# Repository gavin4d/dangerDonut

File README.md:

# Danger Donut

Danger Donut is a work-in-progress 150 gram melty brain combat robot.

This repository contains:
* Code for the operations of the bot
* Code for the IR beacon modulation
* ESC configs
* Main board PCB design
* IR beacon PCB design
* POV display artwork

Links:
* [Bill of Materials](https://docs.google.com/spreadsheets/d/1dkWNEsBBoqDzMkqIhuPgsKdvJ411szMJZwjo1TRifCI/edit?usp=sharing)
* [Full Robot CAD](https://cad.onshape.com/documents/b2161876893824b000416544/w/ad922c252fa114c5bccae0f6/e/2d73a76351a9b656583123fa?renderMode=0&uiState=650de28cdfa14238780e15cb)
* [IR Beacon CAD for Xbox controller](https://cad.onshape.com/documents/fe686b6ebfe56c60cbf11a52/w/a5235571450e0940f943c7f9/e/e1fc86eb24f972fd453b77be?renderMode=0&uiState=650de2660cc6cc1104d13ac3)
* [Transport Box CAD](https://cad.onshape.com/documents/9698310442d8aade0d12c8ac/w/1dfdf825a6ce81e21ee8f0cf/e/f9df83b772e96680fdb5acf9?renderMode=0&uiState=65457ec2115608246b0ef2cf)

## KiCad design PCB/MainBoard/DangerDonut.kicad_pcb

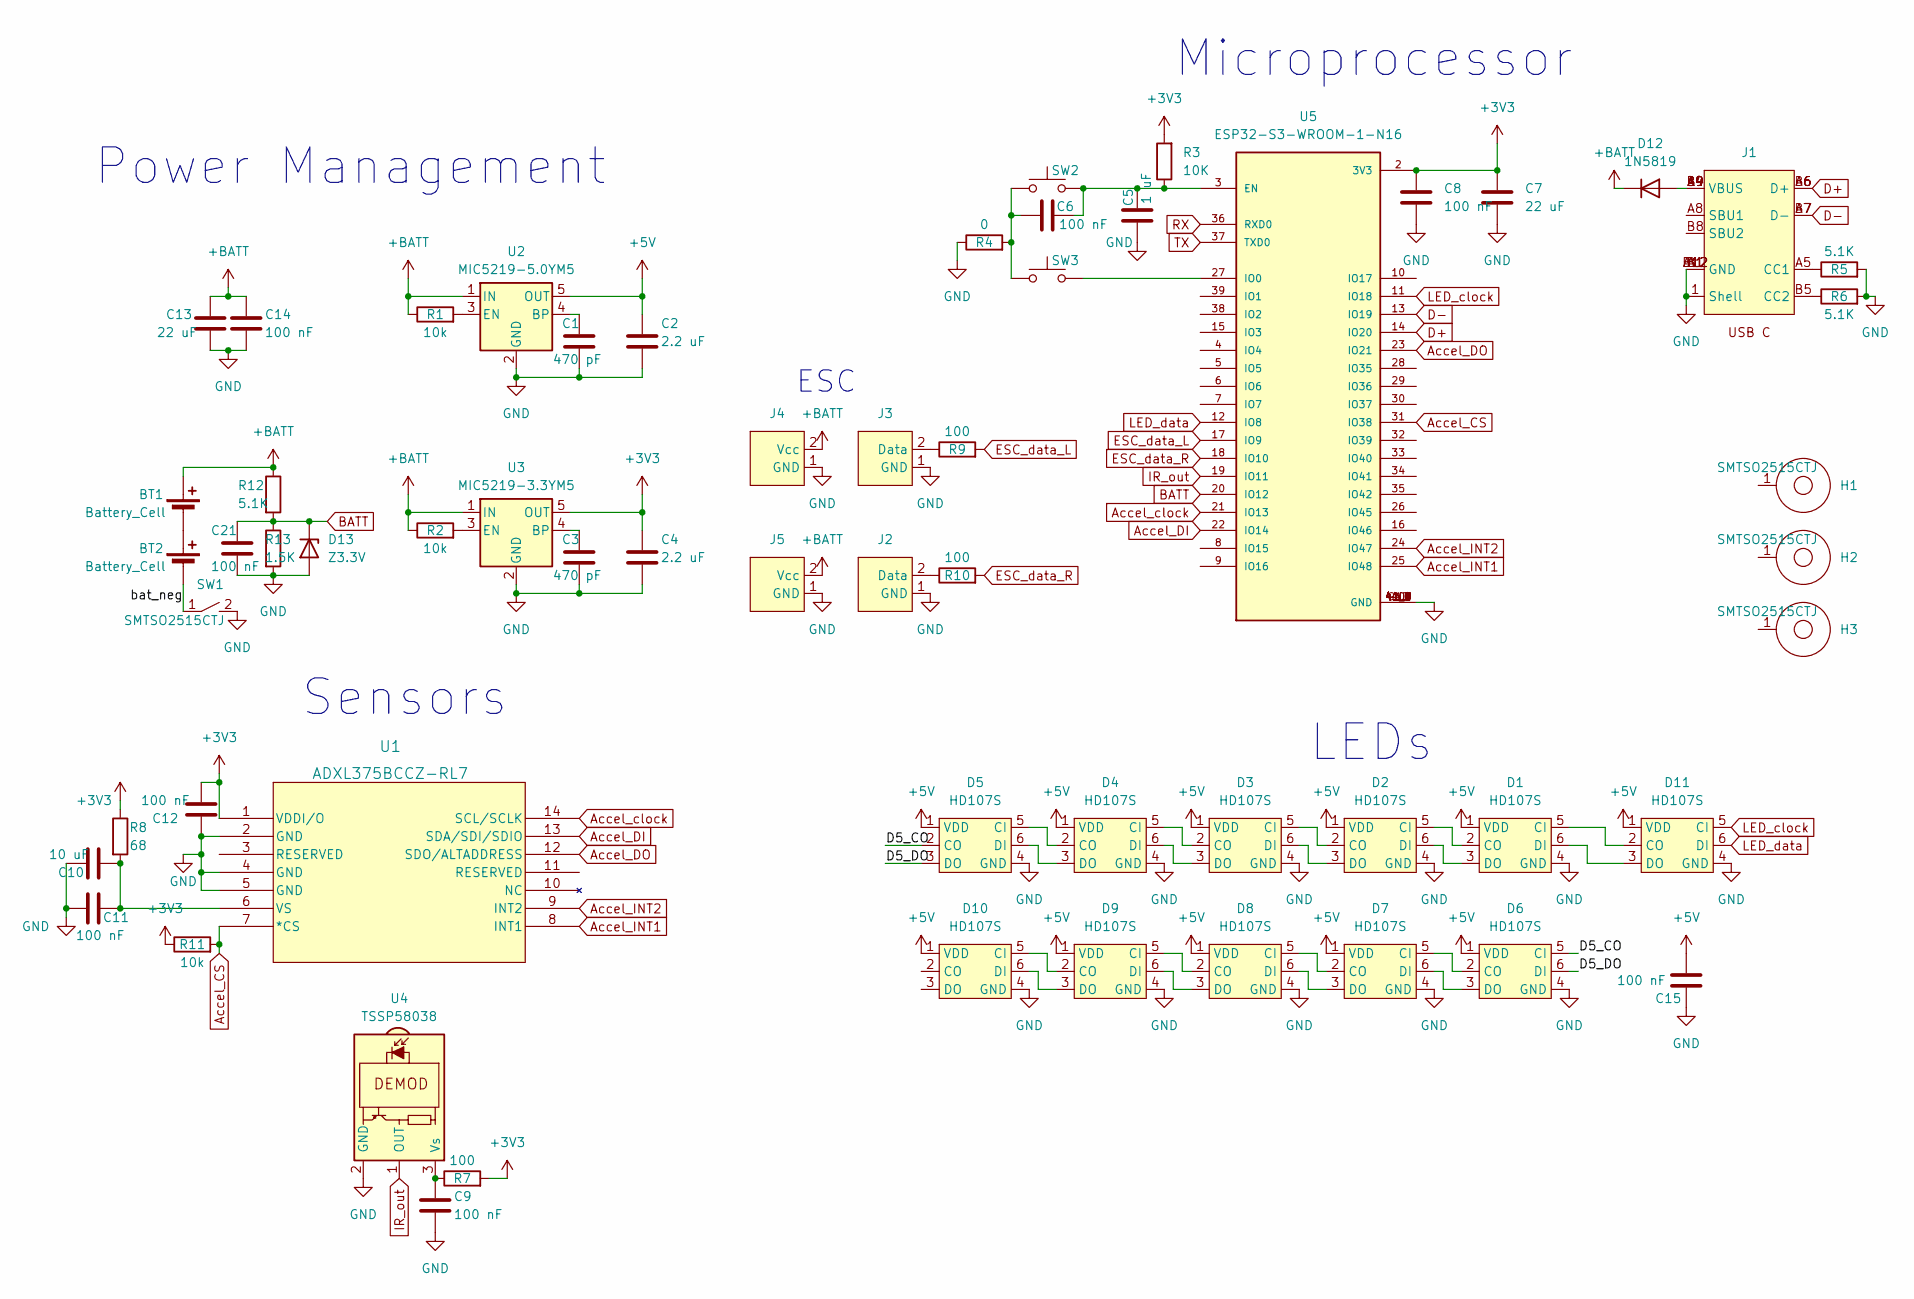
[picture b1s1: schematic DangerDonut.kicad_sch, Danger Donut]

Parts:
BT1, BT2: Battery_Cell; Battery_Solder_Point
C1, C3: 470 pF; C_0603_1608Metric
C2, C4: 2.2 uF; C_0603_1608Metric
C5: 1 uF; C_0603_1608Metric
C6, C8, C9, C11, C12, C14, C15, C21: 100 nF; C_0603_1608Metric
C7, C13: 22 uF; C_1206_3216Metric
C10: 10 uF; C_0805_2012Metric
D1, D2, D3, D4, D5, D6, D7, D8, D9, D10, D11: HD107S
D12: 1N5819; D_SOD-323
D13: Z3.3V; D_MiniMELF; Part ZMM3V3-M
H1, H2, H3: SMTSO2515CTJ; SMTSO2515
J1: TYPE_C_16PLC_H100
J2, J3: ESC_XSD7A_Data
J4, J5: ESC_XSD7A_Power
R1, R2, R11: 10k; R_0603_1608Metric
R3: 10K; R_0603_1608Metric
R4: 0; R_0603_1608Metric; Part 0603WAF0000T5E
R5, R6, R12: 5.1K; R_0603_1608Metric
R7, R9, R10: 100; R_0603_1608Metric
R8: 68; R_0603_1608Metric
R13: 1.5K; R_0603_1608Metric
SW1: SMTSO2515CTJ; SMTSO2515_SW
SW2, SW3: SW_Push; SW_Push_1P1T_XKB_TS-1187A
U1: ADXL375BCCZ-RL7; LGA_CC-14-1_ADI-M
U2: MIC5219-5.0YM5; SOT-23-5
U3: MIC5219-3.3YM5; SOT-23-5
U4: TSSP58038; Vishay_MINICAST-3Pin
U5: ESP32-S3-WROOM-1-N16; XCVR_ESP32-S3-WROOM-1-N16; PARTREV v1.0; DigiKey_Part_Number 1965-ESP32-S3-WROOM-1-N16-ND

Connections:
+3V3: C4.1, C7.1, C8.1, C12.2, R3.2, R7.2, R8.1, R11.1, U1.1 (VDDI/O), U3.5 (OUT), U5.2 (3V3); also elsewhere on the board
+5V: C2.1, C15.2, D1.1 (VDD), D2.1 (VDD), D3.1 (VDD), D4.1 (VDD), D5.1 (VDD), D6.1 (VDD), D7.1 (VDD), D8.1 (VDD), D9.1 (VDD), D10.1 (VDD), D11.1 (VDD), U2.5 (OUT); also elsewhere on the board
+BATT: BT1.1 (+), C13.1, C14.1, D12.1 (K), J4.2 (Vcc), J5.2 (Vcc), R1.1, R2.1, R12.1, U2.1 (IN), U3.1 (IN)
/D5_CO: D5.2 (CO), D6.5 (CI)
/D5_DO: D5.3 (DO), D6.6 (DI)
/bat_neg: BT2.2 (-), SW1.1
Accel_CS: R11.2, U1.7 (*CS), U5.31 (IO38)
Accel_DI: U1.13 (SDA/SDI/SDIO), U5.22 (IO14)
Accel_DO: U1.12 (SDO/ALTADDRESS), U5.23 (IO21)
Accel_INT1: U1.8 (INT1), U5.25 (IO48)
Accel_INT2: U1.9 (INT2), U5.24 (IO47)
Accel_clock: U1.14 (SCL/SCLK), U5.21 (IO13)
BATT: C21.1, D13.1 (K), R12.2, R13.1, U5.20 (IO12)
D+: J1.A6 (D+), J1.B6 (D+), U5.14 (IO20)
D-: J1.A7 (D-), J1.B7 (D-), U5.13 (IO19)
ESC_data_L: R9.2, U5.17 (IO9)
ESC_data_R: R10.2, U5.18 (IO10)
GND: C1.2, C2.2, C3.2, C4.2, C5.2, C7.2, C8.2, C9.2, C10.2, C11.2, C12.1, C13.2, C14.2, C15.1, C21.2, D1.4 (GND), D2.4 (GND), D3.4 (GND), D4.4 (GND), D5.4 (GND), D6.4 (GND), D7.4 (GND), D8.4 (GND), D9.4 (GND), D10.4 (GND), D11.4 (GND), D13.2 (A), J1.1 (Shell), J1.A1 (GND), J1.A12 (GND), J1.B1 (GND), J1.B12 (GND), J2.1 (GND), J3.1 (GND), J4.1 (GND), J5.1 (GND), R4.1, R5.2, R6.2, R13.2, SW1.2, U1.2 (GND), U1.4 (GND), U1.5 (GND), U2.2 (GND), U3.2 (GND), U4.2 (GND), U5.1 (GND), U5.40 (GND), U5.41_1 (GND), U5.41_2 (GND), U5.41_3 (GND), U5.41_4 (GND), U5.41_5 (GND), U5.41_6 (GND), U5.41_7 (GND), U5.41_8 (GND), U5.41_9 (GND), U5.GND; also elsewhere on the board
IR_out: U4.1 (OUT), U5.19 (IO11)
LED_clock: D11.5 (CI), U5.11 (IO18)
LED_data: D11.6 (DI), U5.12 (IO8)
unnamed: BT1.2 (-), BT2.1 (+)
unnamed: C6.1, R4.2, SW2.1, SW3.1
unnamed: D1.5 (CI), D11.2 (CO)
unnamed: D1.2 (CO), D2.5 (CI)
unnamed: D1.6 (DI), D11.3 (DO)
unnamed: D1.3 (DO), D2.6 (DI)
unnamed: D2.2 (CO), D3.5 (CI)
unnamed: D2.3 (DO), D3.6 (DI)
unnamed: D3.2 (CO), D4.5 (CI)
unnamed: D3.3 (DO), D4.6 (DI)
unnamed: D4.2 (CO), D5.5 (CI)
unnamed: D4.3 (DO), D5.6 (DI)
unnamed: D6.2 (CO), D7.5 (CI)
unnamed: D6.3 (DO), D7.6 (DI)
unnamed: D7.2 (CO), D8.5 (CI)
unnamed: D7.3 (DO), D8.6 (DI)
unnamed: D8.2 (CO), D9.5 (CI)
unnamed: D8.3 (DO), D9.6 (DI)
unnamed: D9.2 (CO), D10.5 (CI)
unnamed: D9.3 (DO), D10.6 (DI)
unnamed: D12.2 (A), J1.A4 (VBUS), J1.A9 (VBUS), J1.B4 (VBUS), J1.B9 (VBUS)
unnamed: J1.A5 (CC1), R5.1
unnamed: J1.B5 (CC2), R6.1
unnamed 44: J2.2 (Data), R10.1; also elsewhere on the board
unnamed 45: J3.2 (Data), R9.1; also elsewhere on the board
unnamed: C10.1, C11.1, R8.2, U1.6 (VS)
unnamed: C1.1, U2.4 (BP)
unnamed: R1.2, U2.3 (EN)
unnamed: C3.1, U3.4 (BP)
unnamed: R2.2, U3.3 (EN)
unnamed: C9.1, R7.1, U4.3 (Vs)
unnamed: C5.1, C6.2, R3.1, SW2.2, U5.3 (EN)
unnamed: SW3.2, U5.27 (IO0)
RX: U5.36 (RXD0); also elsewhere on the board
TCK: U5.32 (IO39)
TDI: U5.34 (IO41)
TDO: U5.33 (IO40)
TMS: U5.35 (IO42)
TX: U5.37 (TXD0); also elsewhere on the board

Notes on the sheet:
Power Management
Microprocessor
Sensors
LEDs
ESC

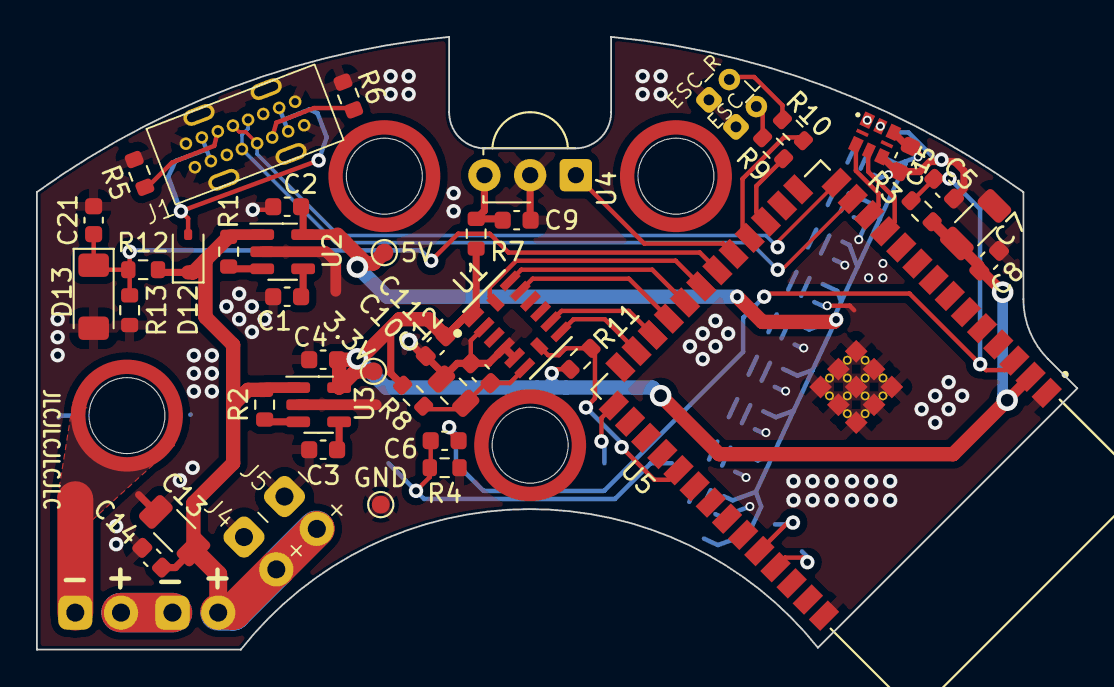
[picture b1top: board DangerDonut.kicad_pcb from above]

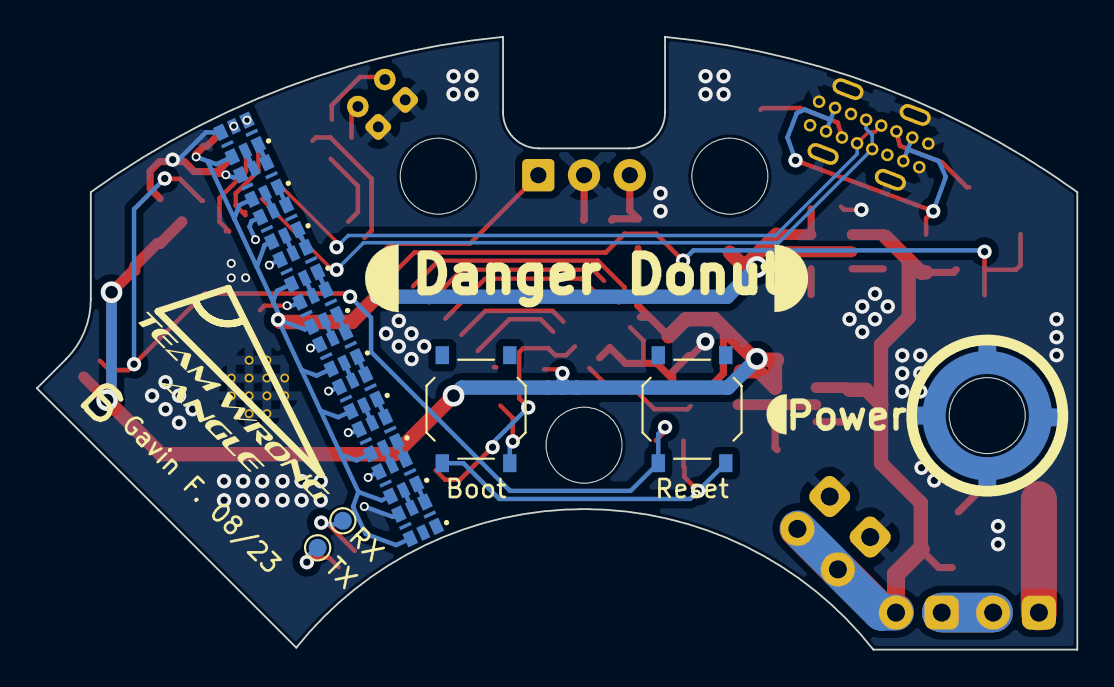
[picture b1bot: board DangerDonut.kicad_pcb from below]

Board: 2 copper layers, 57.8 x 34.0 mm, 65 parts (14 on the bottom side), 56 nets.

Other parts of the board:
3.3V, 5V: TestPoint_Pad_D1.0mm
ESC_L: ESC_XSD7A_Data
ESC_R: ESC_XSD7A_Data
GND: TestPoint_Pad_D1.0mm
RX: TestPoint_Pad_D1.0mm
TX: TestPoint_Pad_D1.0mm

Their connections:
+3V3: 3.3V.1; also elsewhere on the board
+5V: 5V.1; also elsewhere on the board
GND: ESC_L.1 (GND), ESC_R.1 (GND), GND.1; also elsewhere on the board
unnamed 44: ESC_R.2 (Data); also elsewhere on the board
unnamed 45: ESC_L.2 (Data); also elsewhere on the board
RX: RX.1; also elsewhere on the board
TX: TX.1; also elsewhere on the board

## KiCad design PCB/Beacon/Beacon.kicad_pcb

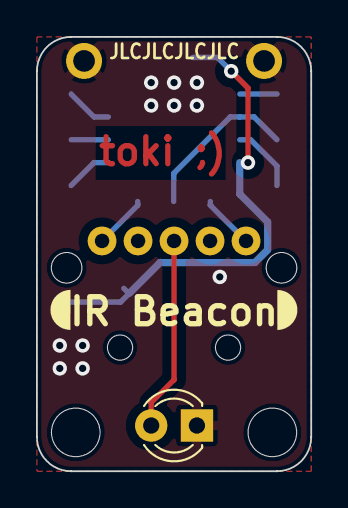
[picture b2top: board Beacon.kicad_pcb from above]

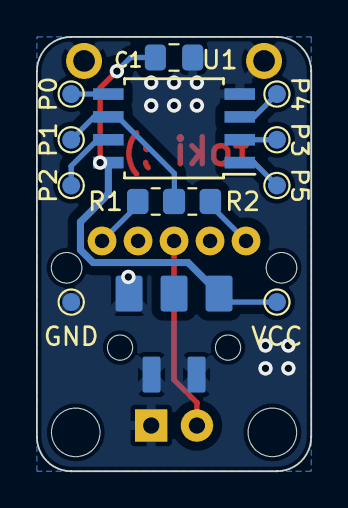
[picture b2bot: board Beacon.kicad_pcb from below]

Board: 2 copper layers, 15.2 x 24.1 mm, 15 parts (13 on the bottom side), 11 nets.

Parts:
BT1: Battery; 3Pin 2.5MM Spring Contact
C1: 1 uF; C_0805_2012Metric_Pad1.18x1.45mm_HandSolder
D1: LED; LED_D3.0mm_Clear
GND: TestPoint; TestPoint_Pad_D1.0mm
P0, P1, P2, P3, P4, P5: TestPoint; TestPoint_Pad_D1.0mm
R1, R2: 47; R_0805_2012Metric_Pad1.20x1.40mm_HandSolder
RV1: R_Potentiometer; Potentiometer_Piher_PC-16_Single_Vertical
U1: ATtiny85-20S; SOIC-8W_5.3x5.3mm_P1.27mm
VCC: TestPoint; TestPoint_Pad_D1.0mm

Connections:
GND: BT1.2 (-), BT1.4, C1.2, D1.1 (K), GND.1, RV1.GND, U1.4 (GND)
unnamed: D1.2 (A), RV1.2
unnamed: R1.2, RV1.1
unnamed: R2.2, RV1.3
unnamed: P0.1, U1.5 (AREF/PB0)
unnamed: P1.1, R1.1, R2.1, U1.6 (PB1)
unnamed: P2.1, U1.7 (PB2)
unnamed: P3.1, U1.2 (XTAL1/PB3)
unnamed: P4.1, U1.3 (XTAL2/PB4)
unnamed: P5.1, U1.1 (~RESET/PB5)
VCC: BT1.1 (+), C1.1, U1.8 (VCC), VCC.1

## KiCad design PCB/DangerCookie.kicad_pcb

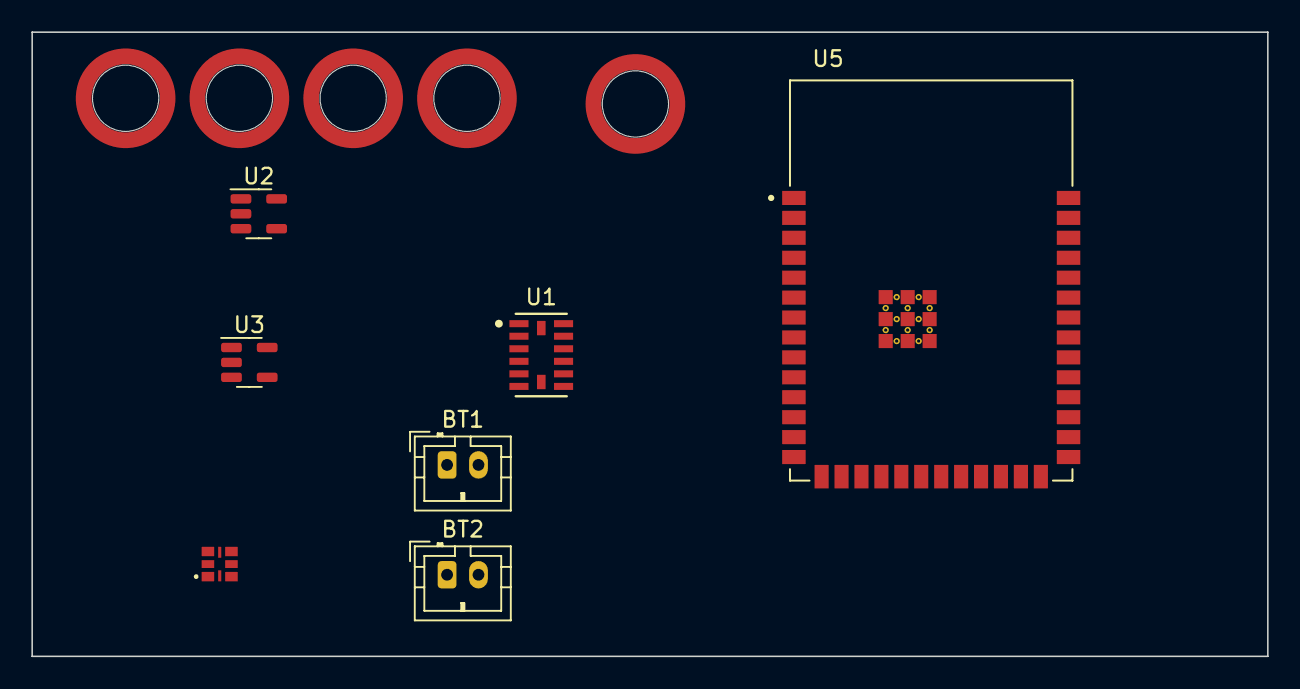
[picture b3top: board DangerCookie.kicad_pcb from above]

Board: 2 copper layers, 78.7 x 39.8 mm, 12 parts (0 on the bottom side), 3 nets, no tracks yet.

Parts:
BT1, BT2: Battery_Cell; JST_PH_B2B-PH-K_1x02_P2.00mm_Vertical
D1: HD107S
H1, H2, H3, H4: SMTSO2515
SW1: SMTSO2515_SW
U1: ADXL375BCCZ-RL7; LGA_CC-14-1_ADI-M
U2: MIC5219-5.0YM5; SOT-23-5
U3: MIC5219-3.3YM5; SOT-23-5
U5: ESP32-S3-WROOM-1-N16; XCVR_ESP32-S3-WROOM-1-N8R2

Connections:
GND: BT2.2 (-), H1.1, H2.1, H3.1, H4.1, U5.1 (GND), U5.40 (GND), U5.41_1 (GND), U5.41_2 (GND), U5.41_3 (GND), U5.41_4 (GND), U5.41_5 (GND), U5.41_6 (GND), U5.41_7 (GND), U5.41_8 (GND), U5.41_9 (GND)
unnamed: BT1.1 (+), SW1.1
unnamed: BT1.2 (-), BT2.1 (+)

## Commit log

2023-08-13 sort of working auto correlation
2023-08-13 simpler auto correlation
2023-08-15 feat: convolution, melty control
2023-08-16 "fixed" apa102, started PCB
2023-08-21 updated PCB
2023-09-17 feat: HD107S LED support
2023-09-17 beacon PCB
2023-09-17 mainBoard PCB
2023-09-17 update to work with HD107S
2023-09-22 Created Readme file
2023-09-22 Added Accelerometer
2023-09-22 HD107S LED driver
2023-10-23 feat: POV display, fixed tracking at low speeds
2023-11-01 feat: kalman filter for orientation
2023-11-01 removed unused components
2023-11-01 feat: 1D LED control, new decorations
2023-11-06 added new decoration
2023-11-28 bug fixes, PID controller
2023-12-06 switched to multi-byte read from ADXL
2023-12-06 feat: flip detection
2024-01-03 new decor, fixed zero offsets, self right
2024-01-07 sdkconfig
2024-03-24 removed PID
2024-03-24 started bt_log (not working)
2024-05-24 Still not working
2024-05-25 missed some files (still not working)
